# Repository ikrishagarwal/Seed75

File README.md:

# Seed75

A completely hand made 75% mechanical keyboard from PCB to case, even the firmware.

## Features

- 75% Layout
- Hot Swappable Sockets
- Sleep Design
- Customizable Push Knob
- USB C Port
- Detachable Angle Elevation
- Sandwich Mount
- Wrist Rest

## Images

### PCB Schematics

### PCB

### PCB Front Layer

### PCB Back Layer

### PCB Rendered Front

### PCB Rendered Back

### Complete Case

### Bottom Case

### Top Case

### Plate

### Elevator

### Wrist Rest

### Knob

### BOM

| Item                                                     | Quantity | Cost (USD)\* | Purchase Link                                                                                                                  |
| -------------------------------------------------------- | -------- | ------------ | ------------------------------------------------------------------------------------------------------------------------------ |
| 1N4148 Diodes                                            | 90 Pack  | 1.52         | https://stackskb.com/store/1n4148-through-hole-diode/                                                                          |
| Akko Bittersweet Switch                                  | 90 Pack  | 33.40        | https://stackskb.com/store/akko-bittersweet-switch-pack-of-45/                                                                 |
| EC11 Rotary Encoder                                      | 1        | 0.43         | https://www.flyrobo.in/ec11-rotary-encoder-half-shaft-handle-potentiometer-15mm                                                |
| Orpheus Pico                                             | 1        |              | Hack Club                                                                                                                      |
| Gateron Hotswap Sockets                                  | 90 Pack  | 10.00        | https://stackskb.com/store/gateron-hotswap-sockets/                                                                            |
| Durock v2 Stabilizers Set                                | 1        | 17.98        | https://stackskb.com/store/durock-clear-screw-in-stabilizers-v2/?attribute_combination=4%2B1+Set&attribute_spacebar-size=6.25U |
| Keycap Set                                               | 1        | 22.21        | https://curiositycaps.in/products/camp-picnic-xvx-p-profile-dye-sub-doubleshot-combination-keycap                              |
| M3x20 Hex CSK Screws                                     | 6x2      | 0.20         | https://omrook.com/ss-allen-csk-m3-x-20mm-dia-3mm-length-20mm-stainless-steel-ss202-allen-socket-countersunk-screws/           |
| M3x6 Hex CSK Screws                                      | 4x2      | 0.05         | https://omrook.com/ss-allen-csk-m3-x-6mm-dia-3mm-length-6mm-stainless-steel-ss202-allen-socket-countersunk-screws/             |
| M3 X 3mm Brass Threaded Inserts                          | 10x2     | 0.83         | https://omrook.com/m3-x-4-brass-threaded-inserts-nut-50pc/                                                                     |
| Bottom Case, Top Case, Plate, Knob, Elevator, Wrist Rest | 1        |              | (3D Printed)                                                                                                                   |
| PCB                                                      | 1        | 56.87        | https://www.pcbpower.com/                                                                                                      |

Cost is as of 01/01/2026

## Software Used

- KiCAD
- Fusion 360

## Author

[Krish](https://github.com/ikrishagarwal)

## License

This project is licensed under the [AGPL-3.0 License](LICENSE).

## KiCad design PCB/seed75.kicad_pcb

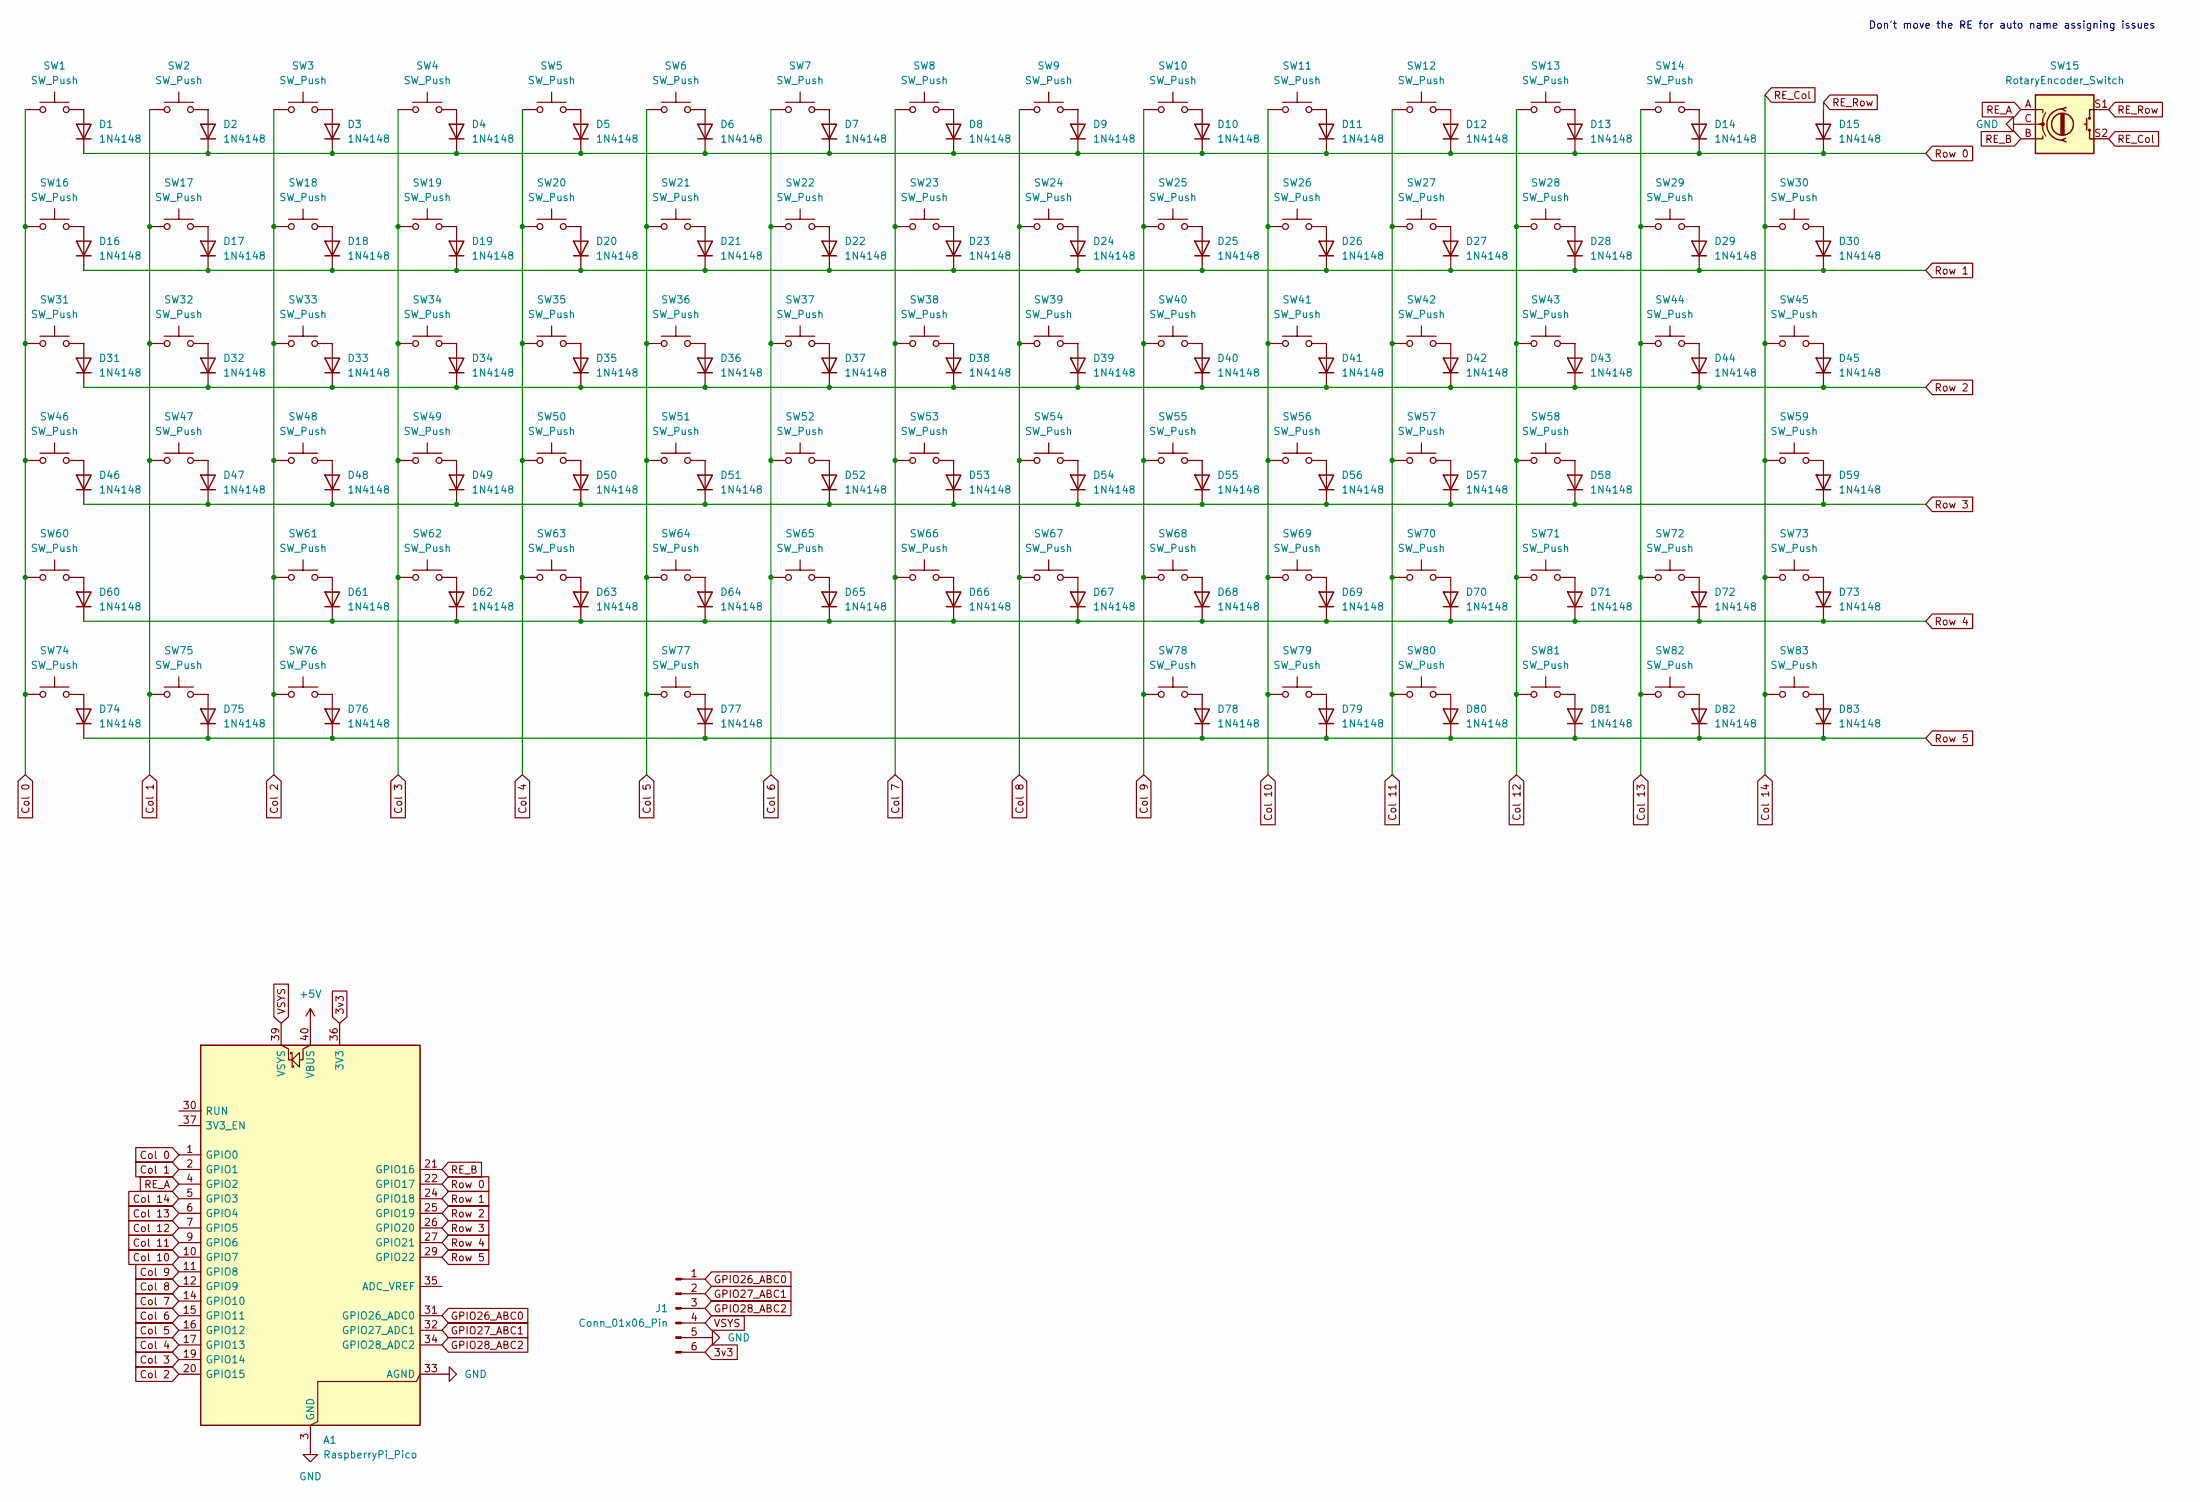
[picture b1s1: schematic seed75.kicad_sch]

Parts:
A1: RaspberryPi_Pico; Raspberry_Pi_Pico
D1, D2, D3, D4, D5, D6, D7, D8, D9, D10, D11, D12, D13, D14, D15, D16, D17, D18, D19, D20, D21, D22, D23, D24, D25, D26, D27, D28, D29, D30, D31, D32, D33, D34, D35, D36, D37, D38, D39, D40, D41, D42, D43, D44, D45, D46, D47, D48, D49, D50, D51, D52, D53, D54, D55, D56, D57, D58, D59, D60, D61, D62, D63, D64, D65, D66, D67, D68, D69, D70, D71, D72, D73, D74, D75, D76, D77, D78, D79, D80, D81, D82, D83: 1N4148; D_DO-35_SOD27_P7.62mm_Horizontal
J1: Conn_01x06_Pin; Wago_734-136_1x06_P3.50mm_Vertical
SW1, SW2, SW3, SW4, SW5, SW6, SW7, SW8, SW9, SW10, SW11, SW12, SW13, SW14, SW16, SW17, SW18, SW19, SW20, SW21, SW22, SW23, SW24, SW25, SW26, SW27, SW28, SW30, SW32, SW33, SW34, SW35, SW36, SW37, SW38, SW39, SW40, SW41, SW42, SW43, SW45, SW47, SW48, SW49, SW50, SW51, SW52, SW53, SW54, SW55, SW56, SW57, SW59, SW61, SW62, SW63, SW64, SW65, SW66, SW67, SW68, SW69, SW70, SW72, SW73, SW78, SW79, SW80, SW81, SW82, SW83: SW_Push; SW_Hotswap_Kailh_MX_Plated_1.00u_With_Switch
SW15: RotaryEncoder_Switch; Encoder_EC11_MX_Combo
SW29: SW_Push; SW_Hotswap_Kailh_MX_Plated_2.00u_With_Switch
SW31, SW44: SW_Push; SW_Hotswap_Kailh_MX_Plated_1.50u_With_Switch
SW46, SW71: SW_Push; SW_Hotswap_Kailh_MX_Plated_1.75u_With_Switch
SW58, SW60: SW_Push; SW_Hotswap_Kailh_MX_Plated_2.25u_With_Switch
SW74, SW75, SW76: SW_Push; SW_Hotswap_Kailh_MX_Plated_1.25u_With_Switch
SW77: SW_Push; SW_Hotswap_Kailh_MX_Plated_6.25u_With_Switch

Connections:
3v3: A1.36 (3V3), J1.6
+5V: A1.40 (VBUS)
Col 0: A1.1 (GPIO0), SW1.1, SW16.1, SW31.1, SW46.1, SW60.1, SW74.1
Col 1: A1.2 (GPIO1), SW2.1, SW17.1, SW32.1, SW47.1, SW75.1
Col 2: A1.20 (GPIO15), SW3.1, SW18.1, SW33.1, SW48.1, SW61.1, SW76.1
Col 3: A1.19 (GPIO14), SW4.1, SW19.1, SW34.1, SW49.1, SW62.1
Col 4: A1.17 (GPIO13), SW5.1, SW20.1, SW35.1, SW50.1, SW63.1
Col 5: A1.16 (GPIO12), SW6.1, SW21.1, SW36.1, SW51.1, SW64.1, SW77.1
Col 6: A1.15 (GPIO11), SW7.1, SW22.1, SW37.1, SW52.1, SW65.1
Col 7: A1.14 (GPIO10), SW8.1, SW23.1, SW38.1, SW53.1, SW66.1
Col 8: A1.12 (GPIO9), SW9.1, SW24.1, SW39.1, SW54.1, SW67.1
Col 9: A1.11 (GPIO8), SW10.1, SW25.1, SW40.1, SW55.1, SW68.1, SW78.1
Col 10: A1.10 (GPIO7), SW11.1, SW26.1, SW41.1, SW56.1, SW69.1, SW79.1
Col 11: A1.9 (GPIO6), SW12.1, SW27.1, SW42.1, SW57.1, SW70.1, SW80.1
Col 12: A1.7 (GPIO5), SW13.1, SW28.1, SW43.1, SW58.1, SW71.1, SW81.1
Col 13: A1.6 (GPIO4), SW14.1, SW29.1, SW44.1, SW72.1, SW82.1
Col 14: A1.5 (GPIO3), SW15.S2, SW30.1, SW45.1, SW59.1, SW73.1, SW83.1
GND: A1.3 (GND), A1.8 (GND), A1.13 (GND), A1.18 (GND), A1.23 (GND), A1.28 (GND), A1.33 (AGND), A1.38 (GND), J1.5, SW15.C
GPIO26_ABC0: A1.31 (GPIO26_ADC0), J1.1
GPIO27_ABC1: A1.32 (GPIO27_ADC1), J1.2
GPIO28_ABC2: A1.34 (GPIO28_ADC2), J1.3
unnamed: D1.2 (A), SW1.2
unnamed: D2.2 (A), SW2.2
unnamed: D3.2 (A), SW3.2
unnamed: D4.2 (A), SW4.2
unnamed: D5.2 (A), SW5.2
unnamed: D6.2 (A), SW6.2
unnamed: D7.2 (A), SW7.2
unnamed: D8.2 (A), SW8.2
unnamed: D9.2 (A), SW9.2
unnamed: D10.2 (A), SW10.2
unnamed: D11.2 (A), SW11.2
unnamed: D12.2 (A), SW12.2
unnamed: D13.2 (A), SW13.2
unnamed: D14.2 (A), SW14.2
unnamed: D16.2 (A), SW16.2
unnamed: D17.2 (A), SW17.2
unnamed: D18.2 (A), SW18.2
unnamed: D19.2 (A), SW19.2
unnamed: D20.2 (A), SW20.2
unnamed: D21.2 (A), SW21.2
unnamed: D22.2 (A), SW22.2
unnamed: D23.2 (A), SW23.2
unnamed: D24.2 (A), SW24.2
unnamed: D25.2 (A), SW25.2
unnamed: D26.2 (A), SW26.2
unnamed: D27.2 (A), SW27.2
unnamed: D28.2 (A), SW28.2
unnamed: D29.2 (A), SW29.2
unnamed: D30.2 (A), SW30.2
unnamed: D31.2 (A), SW31.2
unnamed: D32.2 (A), SW32.2
unnamed: D33.2 (A), SW33.2
unnamed: D34.2 (A), SW34.2
unnamed: D35.2 (A), SW35.2
unnamed: D36.2 (A), SW36.2
unnamed: D37.2 (A), SW37.2
unnamed: D38.2 (A), SW38.2
unnamed: D39.2 (A), SW39.2
unnamed: D40.2 (A), SW40.2
unnamed: D41.2 (A), SW41.2
unnamed: D42.2 (A), SW42.2
unnamed: D43.2 (A), SW43.2
unnamed: D44.2 (A), SW44.2
unnamed: D45.2 (A), SW45.2
unnamed: D46.2 (A), SW46.2
unnamed: D47.2 (A), SW47.2
unnamed: D48.2 (A), SW48.2
unnamed: D49.2 (A), SW49.2
unnamed: D50.2 (A), SW50.2
unnamed: D51.2 (A), SW51.2
unnamed: D52.2 (A), SW52.2
unnamed: D53.2 (A), SW53.2
unnamed: D54.2 (A), SW54.2
unnamed: D55.2 (A), SW55.2
unnamed: D56.2 (A), SW56.2
unnamed: D57.2 (A), SW57.2
unnamed: D58.2 (A), SW58.2
unnamed: D59.2 (A), SW59.2
unnamed: D60.2 (A), SW60.2
unnamed: D61.2 (A), SW61.2
unnamed: D62.2 (A), SW62.2
unnamed: D63.2 (A), SW63.2
unnamed: D64.2 (A), SW64.2
unnamed: D65.2 (A), SW65.2
unnamed: D66.2 (A), SW66.2
unnamed: D67.2 (A), SW67.2
unnamed: D68.2 (A), SW68.2
unnamed: D69.2 (A), SW69.2
unnamed: D70.2 (A), SW70.2
unnamed: D71.2 (A), SW71.2
unnamed: D72.2 (A), SW72.2
unnamed: D73.2 (A), SW73.2
unnamed: D74.2 (A), SW74.2
unnamed: D75.2 (A), SW75.2
unnamed: D76.2 (A), SW76.2
unnamed: D77.2 (A), SW77.2
unnamed: D78.2 (A), SW78.2
unnamed: D79.2 (A), SW79.2
unnamed: D80.2 (A), SW80.2
unnamed: D81.2 (A), SW81.2
unnamed: D82.2 (A), SW82.2
unnamed: D83.2 (A), SW83.2
RE_A: A1.4 (GPIO2), SW15.A
RE_B: A1.21 (GPIO16), SW15.B
RE_Row: D15.2 (A), SW15.S1
Row 0: A1.22 (GPIO17), D1.1 (K), D2.1 (K), D3.1 (K), D4.1 (K), D5.1 (K), D6.1 (K), D7.1 (K), D8.1 (K), D9.1 (K), D10.1 (K), D11.1 (K), D12.1 (K), D13.1 (K), D14.1 (K), D15.1 (K)
Row 1: A1.24 (GPIO18), D16.1 (K), D17.1 (K), D18.1 (K), D19.1 (K), D20.1 (K), D21.1 (K), D22.1 (K), D23.1 (K), D24.1 (K), D25.1 (K), D26.1 (K), D27.1 (K), D28.1 (K), D29.1 (K), D30.1 (K)
Row 2: A1.25 (GPIO19), D31.1 (K), D32.1 (K), D33.1 (K), D34.1 (K), D35.1 (K), D36.1 (K), D37.1 (K), D38.1 (K), D39.1 (K), D40.1 (K), D41.1 (K), D42.1 (K), D43.1 (K), D44.1 (K), D45.1 (K)
Row 3: A1.26 (GPIO20), D46.1 (K), D47.1 (K), D48.1 (K), D49.1 (K), D50.1 (K), D51.1 (K), D52.1 (K), D53.1 (K), D54.1 (K), D55.1 (K), D56.1 (K), D57.1 (K), D58.1 (K), D59.1 (K)
Row 4: A1.27 (GPIO21), D60.1 (K), D61.1 (K), D62.1 (K), D63.1 (K), D64.1 (K), D65.1 (K), D66.1 (K), D67.1 (K), D68.1 (K), D69.1 (K), D70.1 (K), D71.1 (K), D72.1 (K), D73.1 (K)
Row 5: A1.29 (GPIO22), D74.1 (K), D75.1 (K), D76.1 (K), D77.1 (K), D78.1 (K), D79.1 (K), D80.1 (K), D81.1 (K), D82.1 (K), D83.1 (K)
VSYS: A1.39 (VSYS), J1.4

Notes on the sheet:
Don't move the RE for auto name assigning issues

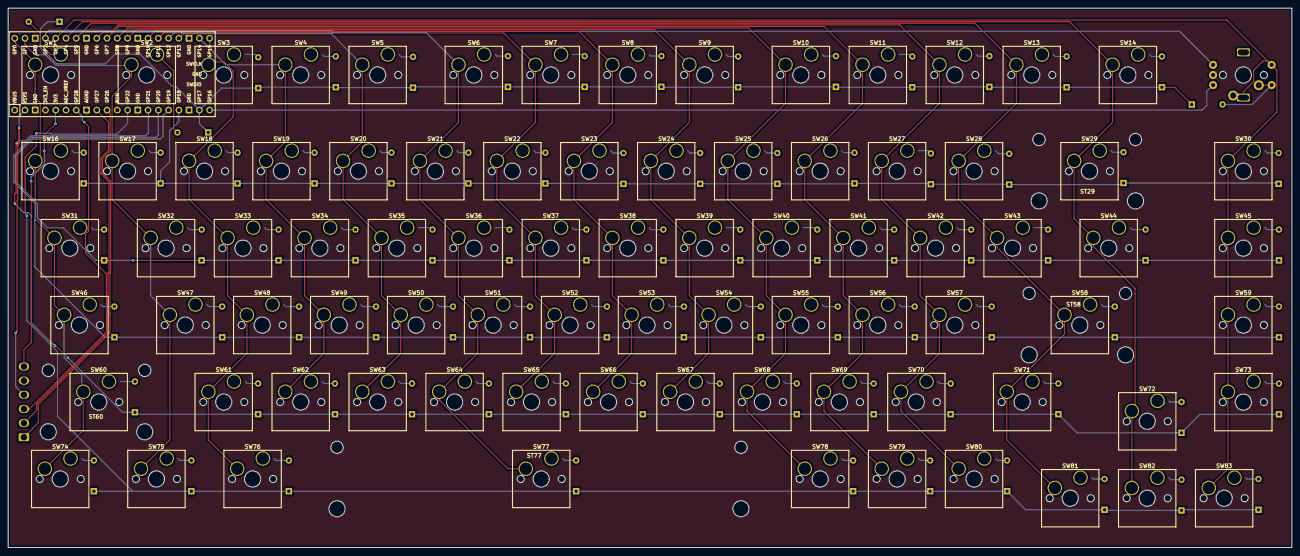
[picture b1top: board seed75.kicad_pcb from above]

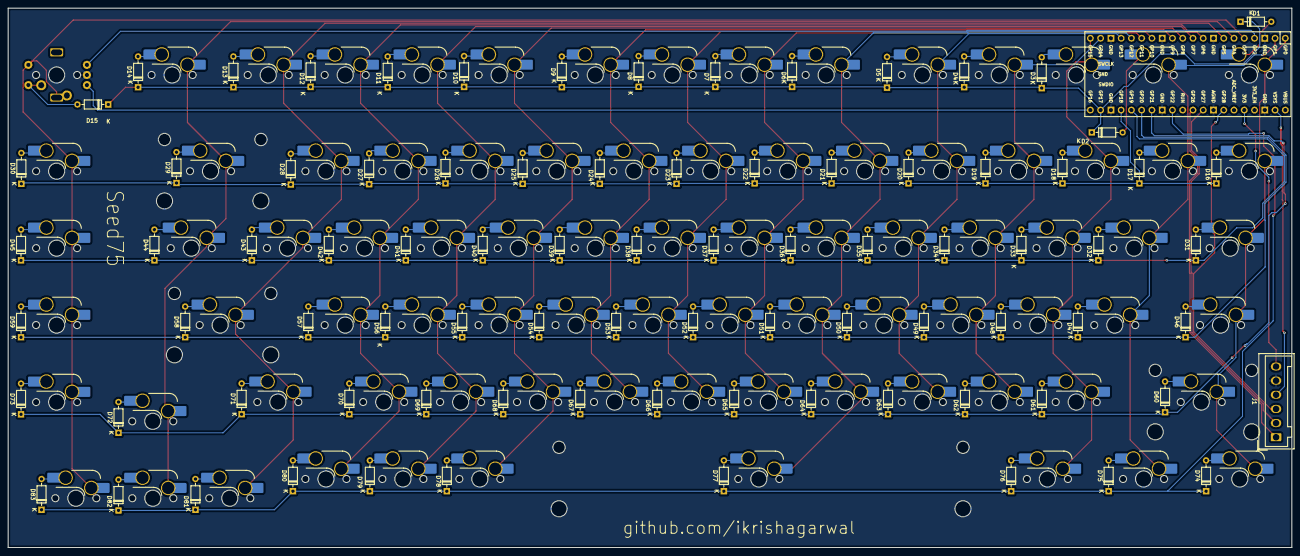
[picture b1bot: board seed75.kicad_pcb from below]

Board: 2 copper layers, 317.8 x 133.5 mm, 172 parts (85 on the bottom side), 112 nets.

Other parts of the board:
ST29, ST58, ST60: Stabilizer_Cherry_MX_2.00u
ST77: Stabilizer_Cherry_MX_6.25u

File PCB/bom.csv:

Id,Designator,Footprint,Quantity,Designation,Supplier and ref
1,"SW65,SW67,SW33,SW11,SW14,SW25,SW69,SW36,SW7,SW82,SW56,SW21,SW3,SW72,SW68,SW13,SW12,SW53,SW49,SW47,SW23,SW70,SW78,SW51,SW27,SW30,SW73,SW61,SW32,SW1,SW55,SW20,SW80,SW83,SW79,SW50,SW52,SW62,SW10,SW5,SW57,SW42,SW45,SW66,SW41,SW34,SW6,SW35,SW39,SW59,SW40,SW64,SW18,SW63,SW9,SW22,SW17,SW16,SW8,SW4,SW19,SW28,SW48,SW38,SW54,SW24,SW81,SW37,SW43,SW26,SW2","SW_Hotswap_Kailh_MX_Plated_1.00u_With_Switch",71,SW_Push,
2,"SW75,SW76,SW74","SW_Hotswap_Kailh_MX_Plated_1.25u_With_Switch",3,SW_Push,
3,"SW31,SW44","SW_Hotswap_Kailh_MX_Plated_1.50u_With_Switch",2,SW_Push,
4,"SW58,SW60","SW_Hotswap_Kailh_MX_Plated_2.25u_With_Switch",2,SW_Push,
5,"SW15","Encoder_EC11_MX_Combo",1,RotaryEncoder_Switch,
6,"SW29","SW_Hotswap_Kailh_MX_Plated_2.00u_With_switch",1,SW_Push,
7,"SW77","SW_Hotswap_Kailh_MX_Plated_6.25u_With_Switch",1,SW_Push,
8,"SW71,SW46","SW_Hotswap_Kailh_MX_Plated_1.75u_With_Switch",2,SW_Push,
9,"D55,D66,D44,D28,D37,D82,D10,D41,D15,D38,D34,D72,D4,D26,D78,D39,D80,D27,D83,D11,D50,D14,D77,D68,D21,D8,D71,D40,D42,D47,D2,D23,D35,D17,D67,D64,D74,D79,D65,D9,D63,D18,D52,D29,D81,D16,D5,D1,D25,D53,D59,D19,D30,D6,D45,D57,D22,D48,D24,D49,D31,D62,D36,D3,D46,D51,D32,D12,D33,D20,D56,D60,D76,D54,D7,D75,D70,D13,D58,D73,D61,D69,D43","D_DO-35_SOD27_P7.62mm_Horizontal",83,1N4148,
10,"A1","RaspberryPi_Pico_Common_Unspecified",1,RaspberryPi_Pico,
11,"J1","Wago_734-136_1x06_P3.50mm_Vertical",1,Conn_01x06_Pin,

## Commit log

2025-10-12 feat: adds the case and pcb
2025-10-13 feat: completes readme
2025-10-27 fix: case design issues
2025-10-28 feat: rough firmware in KMK
2025-10-28 fix: BOM list
2025-11-05 feat: updated PCB files
2025-11-05 docs: updated the BOM list
2025-11-05 feat: updated images and knob
2025-11-26 feat: adds production folder
2026-01-01 feat: updated BOM
2026-01-01 fix: csv issues
2026-01-02 feat: fixed to pcb
2026-01-02 fix: pcb changes
2026-01-05 chore: changed the provider for screws
